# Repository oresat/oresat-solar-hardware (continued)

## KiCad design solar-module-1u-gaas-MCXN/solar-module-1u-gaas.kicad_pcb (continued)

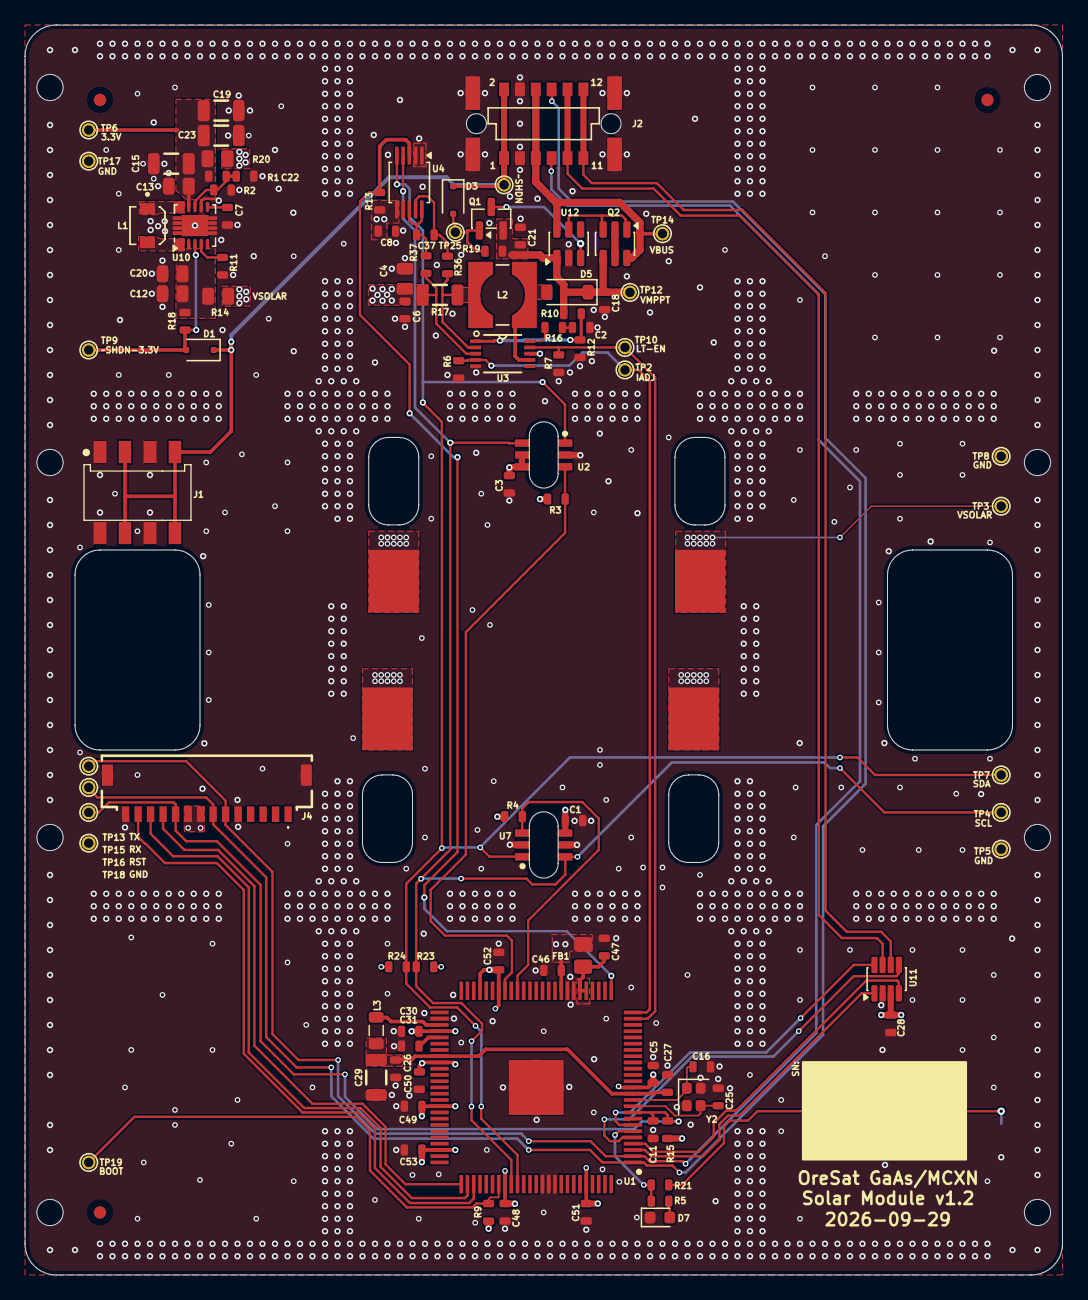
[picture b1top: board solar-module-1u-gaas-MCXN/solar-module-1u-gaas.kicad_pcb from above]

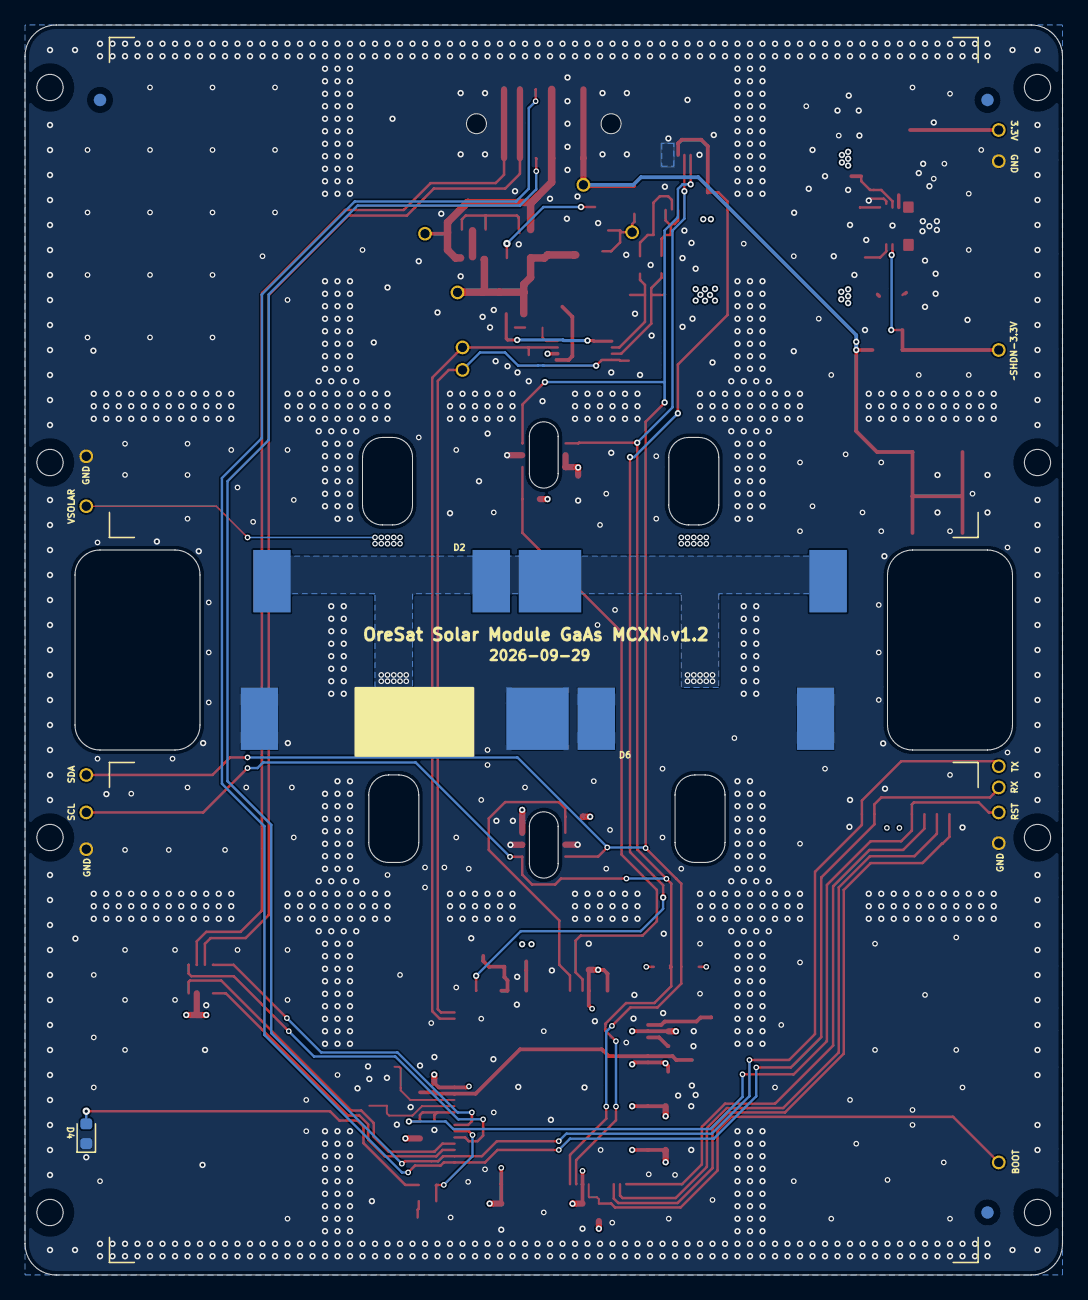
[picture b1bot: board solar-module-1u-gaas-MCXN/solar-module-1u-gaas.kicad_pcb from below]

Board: 4 copper layers, 83.0 x 100.0 mm, 110 parts (6 on the bottom side), 55 nets.

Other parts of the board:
PCB1: ORESAT-SOLAR-BOARD-V1.0-SILICON-CELLS; ORESAT-SOLAR-BOARD-V4

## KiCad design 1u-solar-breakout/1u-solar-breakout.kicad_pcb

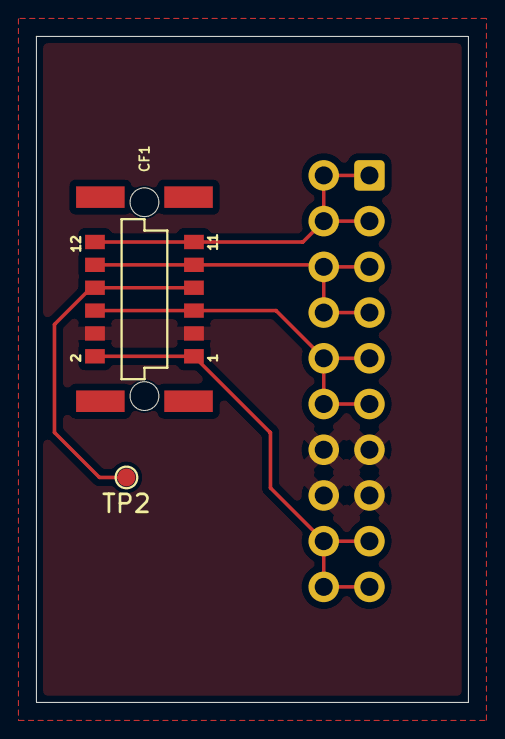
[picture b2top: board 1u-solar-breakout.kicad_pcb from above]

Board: 2 copper layers, 24.0 x 37.0 mm, 3 parts (1 on the bottom side), 6 nets.

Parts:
CF1: J-Harwin-M55-60X1242R
J3: 302-S201; IDC-Header_2x10_P2.54mm_Vertical
TP2: TEST-POINT-LARGE-SQUARE; TestPoint_Pad_D1.0mm

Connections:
GND: CF1.3 (GND), CF1.4 (GND), J3.13, J3.14, J3.15, J3.16
unnamed: CF1.7 (AUX), CF1.8 (AUX), TP2.1 (1_1)
unnamed: CF1.11 (CANL), CF1.12 (CANL), J3.1, J3.2, J3.3, J3.4
unnamed: CF1.9 (CANH), CF1.10 (CANH), J3.5, J3.6, J3.7, J3.8
unnamed: CF1.5 (VBUS), CF1.6 (VBUS), J3.9, J3.10, J3.11, J3.12
unnamed: CF1.1 (~SD), CF1.2 (~SD), J3.17, J3.18, J3.19, J3.20

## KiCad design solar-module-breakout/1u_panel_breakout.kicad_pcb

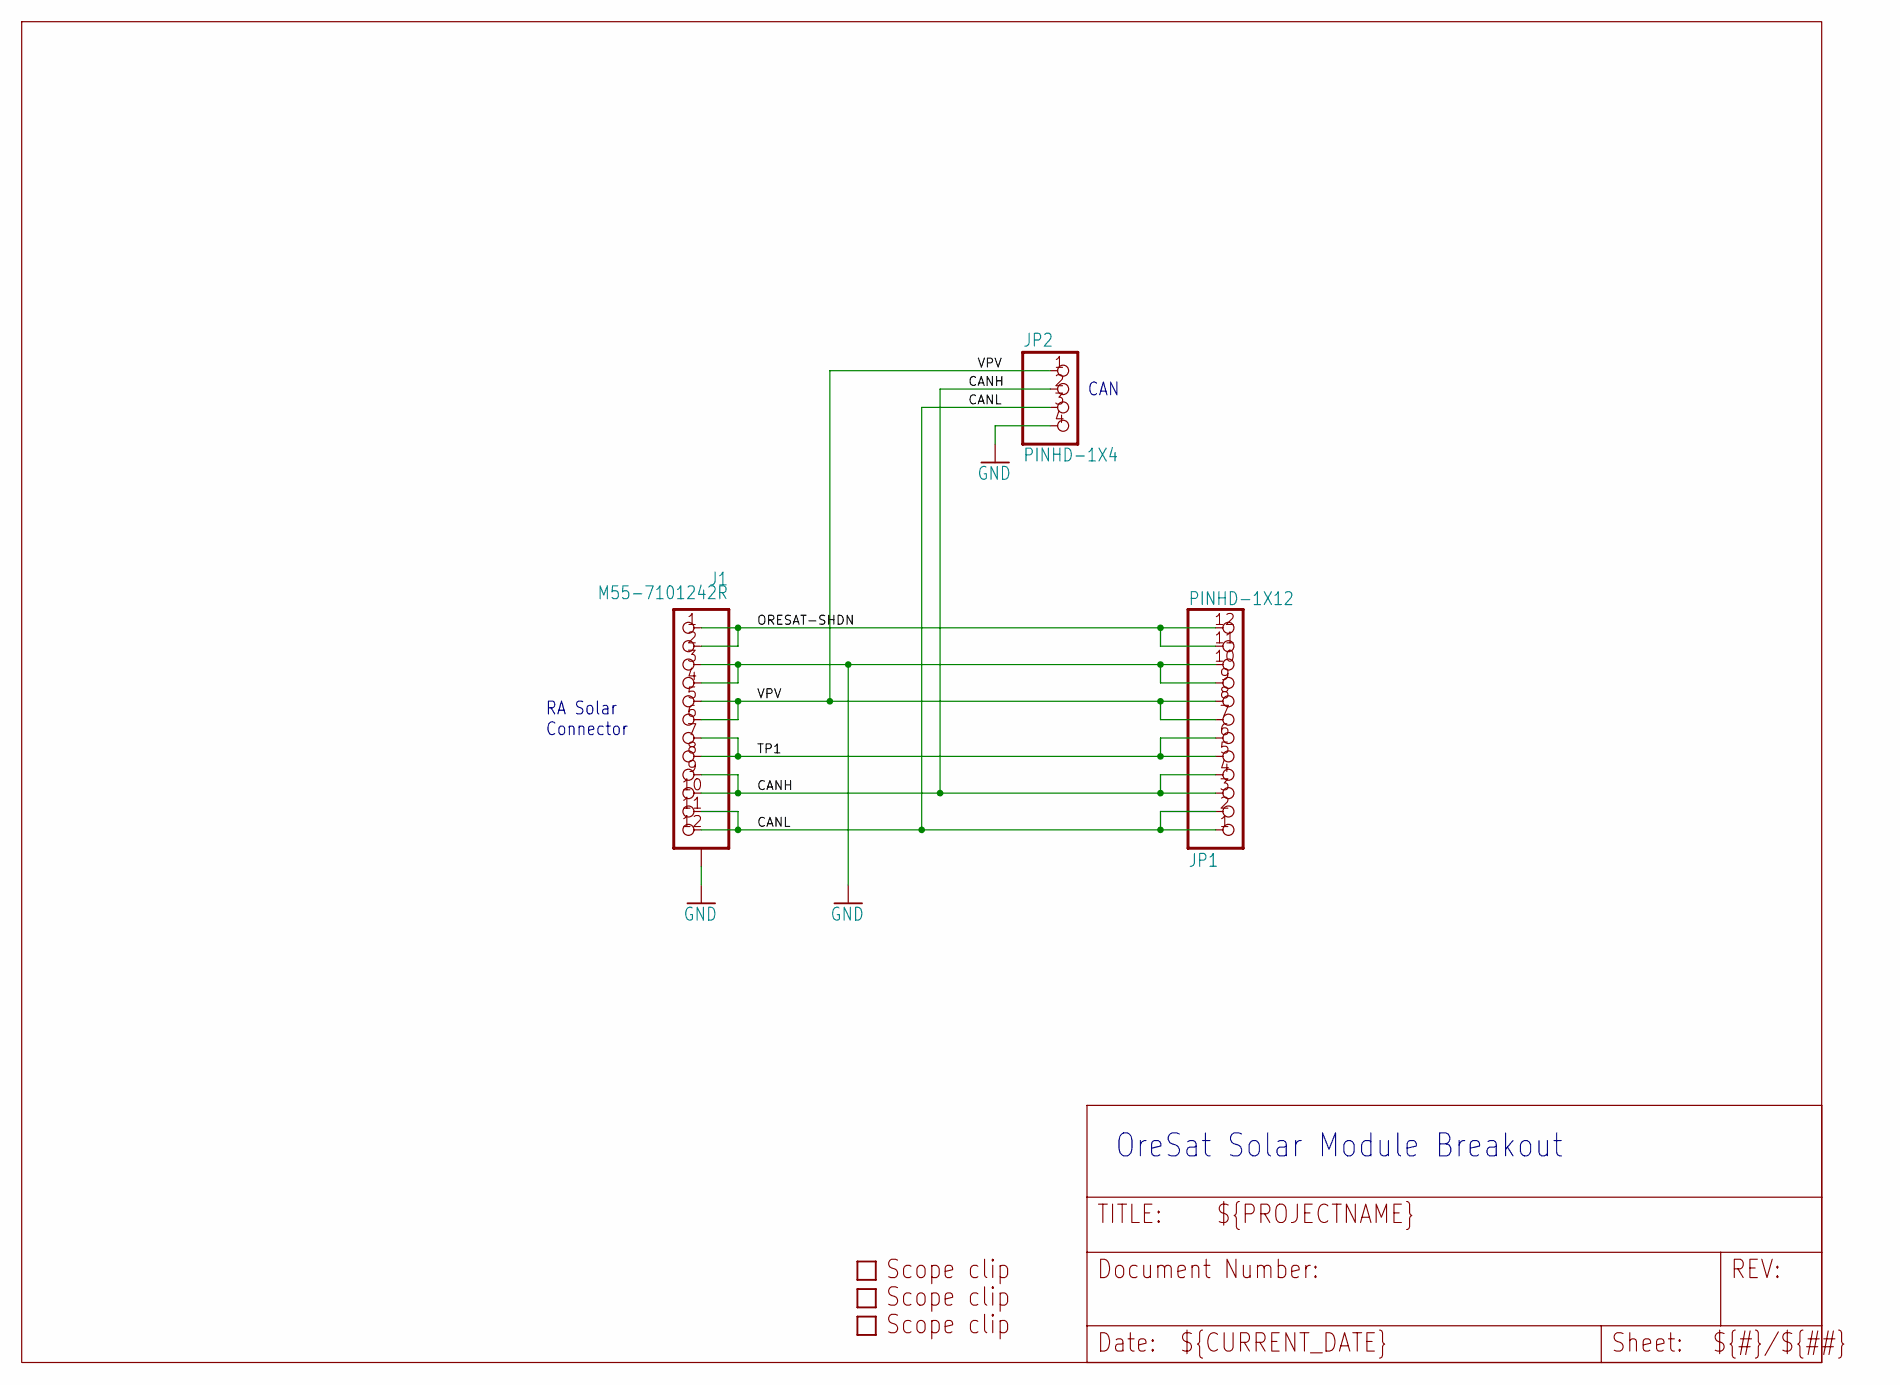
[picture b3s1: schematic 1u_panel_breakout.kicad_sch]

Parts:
J1: M55-7101242R
JP1: PINHD-1X12; 1X12
JP2: PINHD-1X4; 1X04
U$1, U$2, U$3: SCOPE_CLIP

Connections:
CANH: J1.9, J1.10, JP1.3, JP1.4, JP2.2
CANL: J1.11, J1.12, JP1.1, JP1.2, JP2.3
GND: J1.3, J1.4, J1.P$1 (SHIELD), J1.P$2 (SHIELD), J1.P$3 (SHIELD), J1.P$4 (SHIELD), JP1.9, JP1.10, JP2.4
ORESAT-SHDN: J1.1, J1.2, JP1.11, JP1.12
TP1: J1.7, J1.8, JP1.5, JP1.6
VPV: J1.5, J1.6, JP1.7, JP1.8, JP2.1

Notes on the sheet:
CAN
OreSat Solar Module Breakout
RA Solar Connector

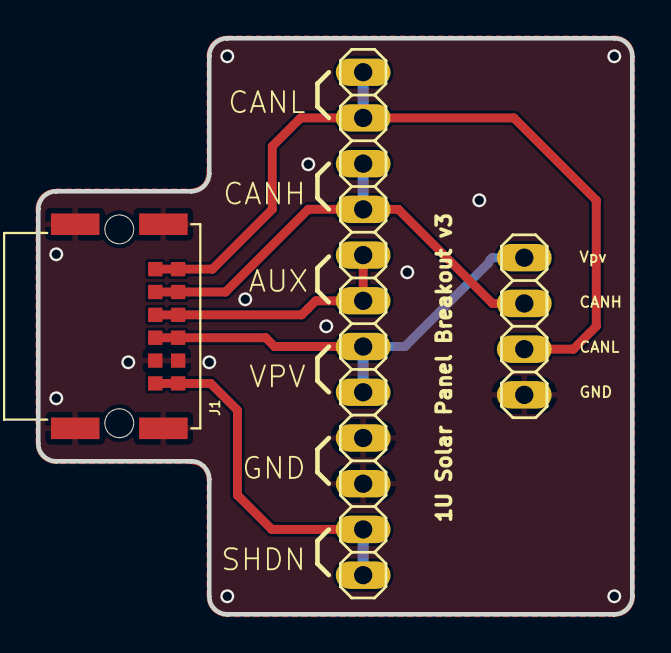
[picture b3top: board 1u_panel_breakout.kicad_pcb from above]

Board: 2 copper layers, 33.0 x 32.0 mm, 6 parts (0 on the bottom side), 6 nets.

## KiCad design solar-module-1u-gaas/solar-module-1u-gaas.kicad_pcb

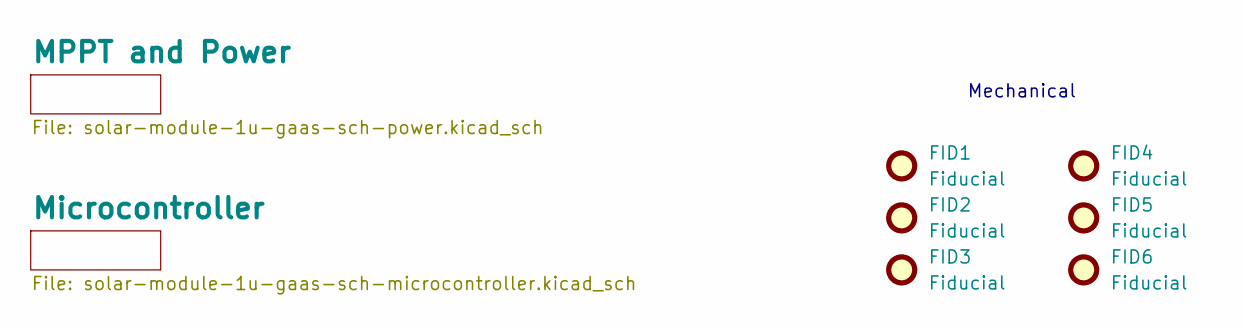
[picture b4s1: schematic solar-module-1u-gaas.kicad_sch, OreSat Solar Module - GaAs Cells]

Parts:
FID1, FID2, FID3, FID4, FID5, FID6: Fiducial; Fiducial_1mm_Mask2mm

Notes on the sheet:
Mechanical

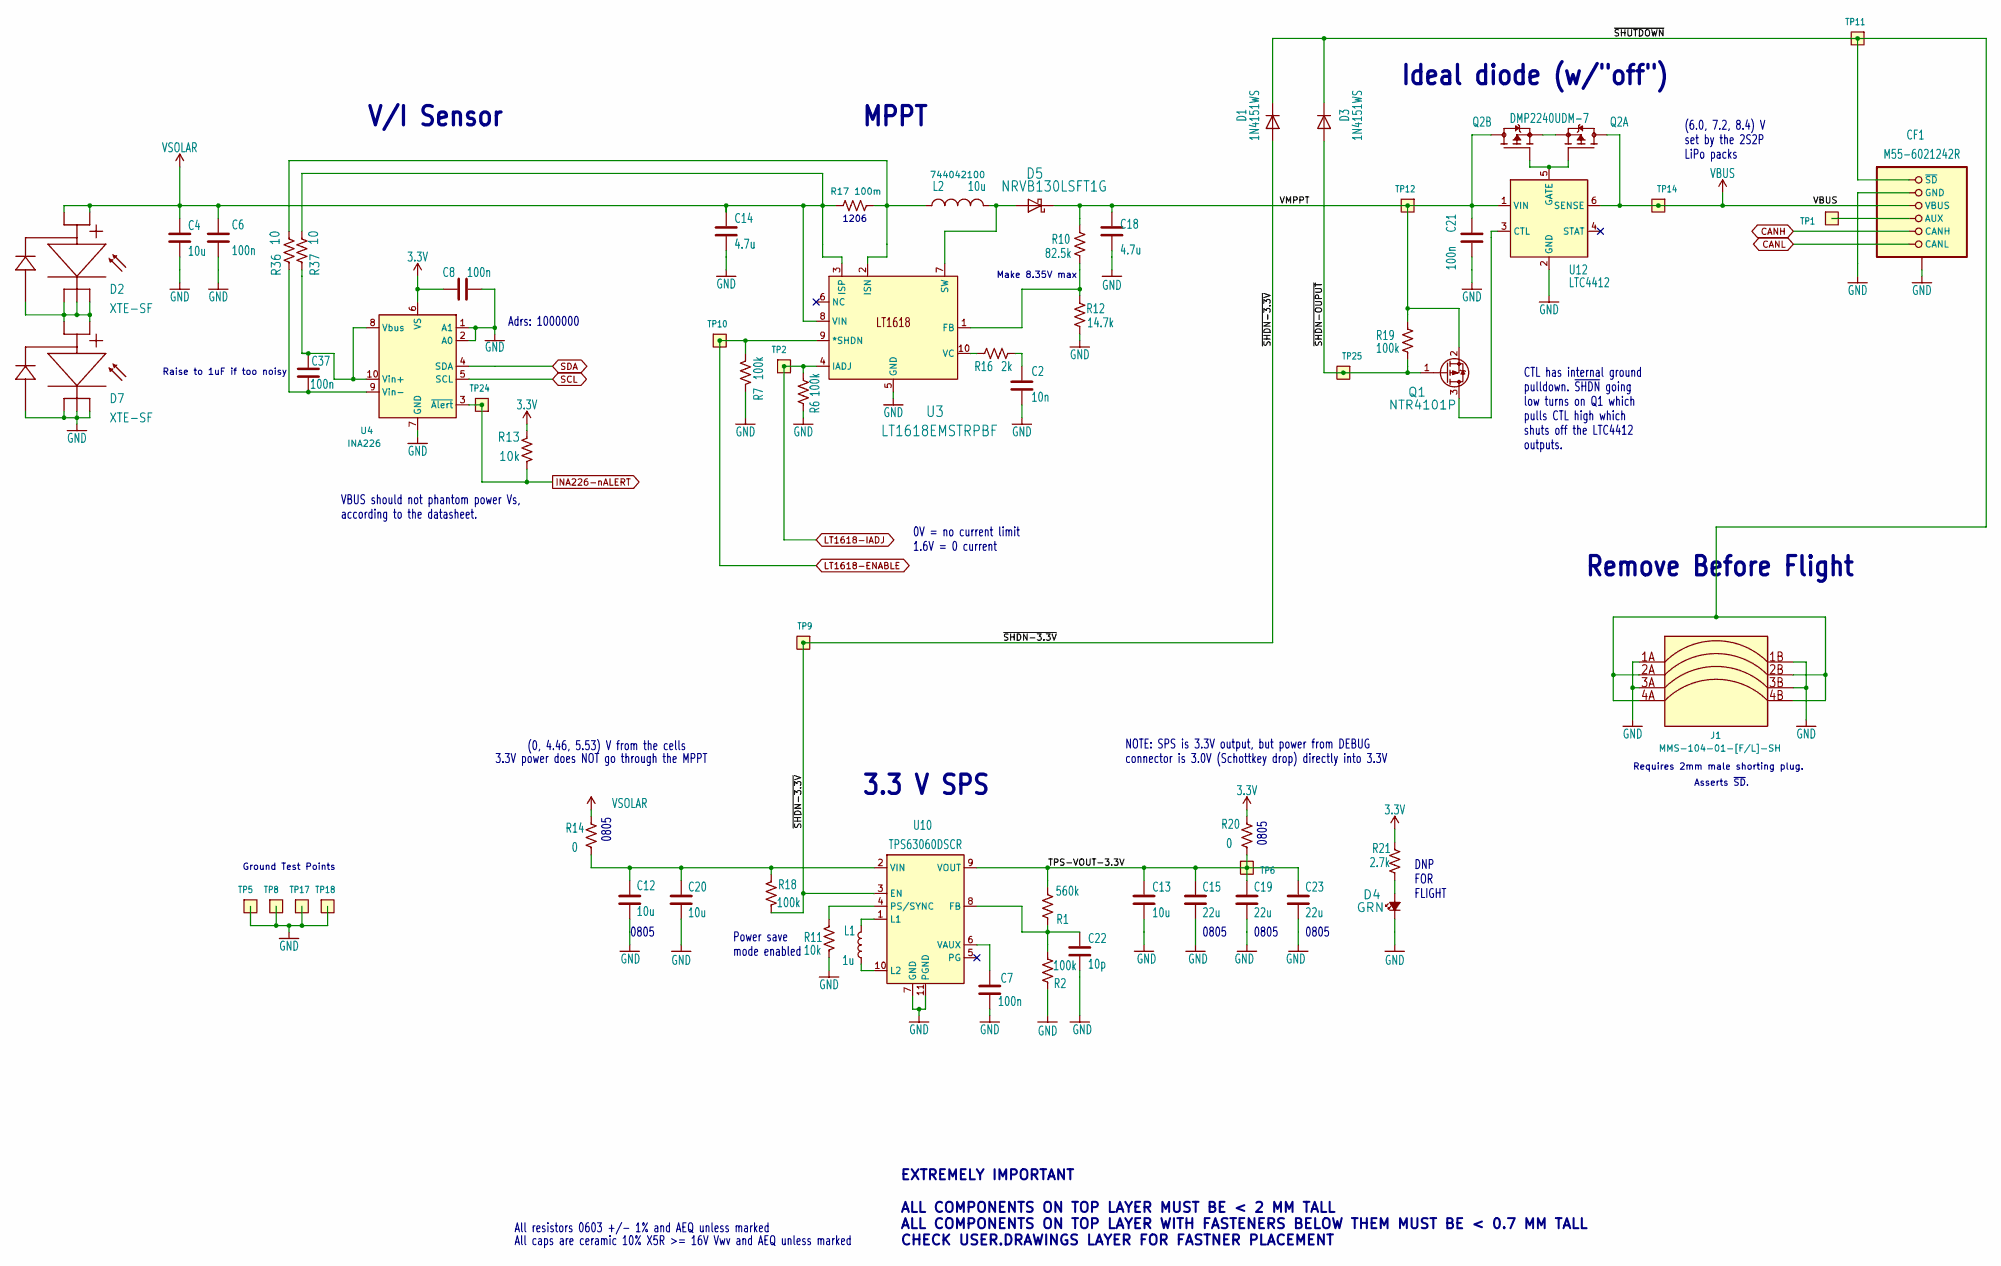
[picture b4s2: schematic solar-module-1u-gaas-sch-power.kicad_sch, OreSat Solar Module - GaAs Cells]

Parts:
C2: 10n; 0603-C-NOSILK; MPN C0603C103J3GECAUTO
C4, C13, C20: 10u; 0603-C-NOSILK; MPN GRT188R61C106KE13D
C6, C7, C8, C21, C37: 100n; 0603-C-NOSILK; MPN TMK107BJ104KAHT
C12: 10u; 0805-C-NOSILK; MPN GRT21BC71E106KE13L
C14, C18: 4.7u; 0603-C-NOSILK; MPN CL10A475KO8NNNC
C15, C19, C23: 22u; 0805-C-NOSILK; MPN 490-12389-2-ND
C22: 10p; 0603-C-NOSILK; MPN C0603C100J5GACAUTO
CF1: M55-6021242R; J-Harwin-M55-60X1242R; MPN M55-6021242R
D1, D3: 1N4151WS; D-SOD323-R; MPN 1N4151WS-E3-08
D2, D7: XTE-SF; SPECTROLAB-XTE-SF
D4: GRN; LED_0603_1608Metric; MPN 150060GS75000
D5: NRVB130LSFT1G; D_SOD-123; MPN NRVB130LSFT1G
J1: MMS-104-01-[F/L]-SH; SAMTEC-MMS-104-02-X-SH; MPN MMS-104-02-L-SH
L1: 1u; IND_1226AS-H-1R0N=P2; MPN 1227AS-H-1R0N=P2
L2: 10u; 744042100; MPN 744042100
Q1: NTR4101P; SOT-23; MPN NTR4101PT1G
Q2: DMP2240UDM-7; SOT-23-6; MPN DMP2240UDM-7
R1: 560k; 0603-C-NOSILK; MPN RMCF0603FT560K
R2, R6, R7, R18, R19: 100k; 0603-C-NOSILK; MPN RMCF0603FT100K
R10: 82.5k; 0603-C-NOSILK; MPN RMCF0603FT82K5
R11, R13: 10k; 0603-C-NOSILK; MPN RMCF0603FT10K0
R12: 14.7k; 0603-C-NOSILK; MPN RMCF0603FT14K7
R14, R20: 0; 0805-C-NOSILK; MPN ERJ-6GEY0R00V
R16: 2k; 0603-C-NOSILK; MPN RMCF0603FT2K00
R17: 100m; 1206-C; MPN CSR1206FTR100
R21: 2.7k; 0603-C-NOSILK; MPN RMCF0603FT2K70
R36, R37: 10; 0603-C-NOSILK; MPN RMCF0603FT10R0
TP1, TP2, TP5, TP6, TP8, TP9, TP10, TP11, TP12, TP14, TP17, TP18, TP24, TP25: TEST-POINT-LARGE-SQUARE; TestPoint-0.75mm-th
U3: LT1618EMSTRPBF; MSOP-10_MS; MPN IC REG BOOST ADJ 1.5A 10MSOP
U4: INA226; VSSOP-10_3x3mm_P0.5mm; MPN INA226AIDGST
U10: TPS63060DSCR; Texas_S-PWSON-N10; MPN IC REG BUCK BOOST ADJ 2A 10WSON
U12: LTC4412; TSOT-23-6; MPN LTC4412ES6#TRPBF

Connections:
3.3V: C8.1, R13.2, R20.1, R21.1, U4.6 (VS); also elsewhere on the board
/MPPT and Power/TPS-VOUT-3.3V: C13.1, C15.1, C19.1, C23.1, R1.2, R20.2, TP6.1, U10.9 (VOUT)
/MPPT and Power/VMPPT: C18.1, C21.1, D5.1 (K), Q1.2 (S), Q2.4 (D), R10.2, R19.2, TP12.1, U12.1 (VIN)
/MPPT and Power/~SHDN-3.3V: D1.2 (A), R18.1, TP9.1, U10.3 (EN)
/MPPT and Power/~SHDN-OUPUT: D3.2 (A), Q1.1 (G), R19.1, TP25.1
/MPPT and Power/~SHUTDOWN: CF1.1 (~SD), CF1.2 (~SD), D1.1 (K), D3.1 (K), J1.2A, J1.2B, J1.4A, J1.4B, TP11.1
CANH: CF1.9 (CANH), CF1.10 (CANH); also elsewhere on the board
CANL: CF1.11 (CANL), CF1.12 (CANL); also elsewhere on the board
GND: C2.2, C4.2, C6.2, C7.2, C8.2, C12.2, C13.2, C14.2, C15.2, C18.2, C19.2, C20.2, C21.2, C22.2, C23.2, CF1.3 (GND), CF1.4 (GND), CF1.P$1 (SHIELD), CF1.P$2 (SHIELD), CF1.P$3 (SHIELD), CF1.P$4 (SHIELD), D4.1 (K), D7.NEG1 (C1), D7.NEG2 (C2), D7.NEG3 (C3), D7.NEG4 (C4), J1.1A, J1.1B, J1.3A, J1.3B, R2.1, R6.2, R7.2, R11.1, R12.1, TP5.1, TP8.1, TP17.1, TP18.1, U3.5 (GND), U4.1 (A1), U4.2 (A0), U4.7 (GND), U10.7 (GND), U10.11 (PGND), U12.2 (GND); also elsewhere on the board
INA226-nALERT: R13.1, TP24.1, U4.3 (~Alert); also elsewhere on the board
LT1618-ENABLE: R7.1, TP10.1, U3.9 (*SHDN); also elsewhere on the board
LT1618-IADJ: R6.1, TP2.1, U3.4 (IADJ); also elsewhere on the board
unnamed: C2.1, R16.1
unnamed: CF1.7 (AUX), CF1.8 (AUX), TP1.1
unnamed: D2.NEG1 (C1), D2.NEG2 (C2), D2.NEG3 (C3), D2.NEG4 (C4), D7.POS1 (A1), D7.POS2 (A2)
unnamed: D4.2 (A), R21.2
unnamed: D5.2 (A), L2.2, U3.7 (SW)
unnamed: Q1.3 (D), U12.3 (CTL)
unnamed: Q2.1 (G), Q2.3 (G), U12.5 (GATE)
unnamed: Q2.2 (S), Q2.5 (S)
unnamed: R10.1, R12.2, U3.1 (FB)
unnamed: L2.1, R17.2, R36.1, U3.2 (ISN)
unnamed: R16.2, U3.10 (VC)
unnamed: C37.1, R37.1, U4.8 (Vbus), U4.10 (Vin+)
unnamed: C37.2, R36.2, U4.9 (Vin-)
unnamed: C22.1, R1.1, R2.2, U10.8 (FB)
unnamed: L1.2, U10.1 (L1)
unnamed: L1.1, U10.10 (L2)
unnamed: R11.2, U10.4 (PS/SYNC)
unnamed: C7.1, U10.6 (VAUX)
unnamed: C12.1, C20.1, R14.1, R18.2, U10.2 (VIN)
SCL: U4.5 (SCL); also elsewhere on the board
SDA: U4.4 (SDA); also elsewhere on the board
VBUS: CF1.5 (VBUS), CF1.6 (VBUS), Q2.6 (D), TP14.1, U12.6 (SENSE)
VSOLAR: C4.1, C6.1, C14.1, D2.POS1 (A1), D2.POS2 (A2), R14.2, R17.1, R37.2, U3.3 (ISP), U3.8 (VIN)

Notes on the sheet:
DNP FOR FLIGHT
0805
CTL has internal ground pulldown. ~{SHDN} going low turns on Q1 which pulls CTL high which shuts off the LTC4412 outputs.
(0, 4.46, 5.53) V from the cells
Ground Test Points
Make 8.35V max
Asserts ~{SD}.
Raise to 1uF if too noisy
All resistors 0603 +/- 1% and AEQ unless marked
NOTE: SPS is 3.3V output, but power from DEBUG connector is 3.0V (Schottkey drop) directly into 3.3V
Power save mode enabled
3.3 V SPS
EXTREMELY IMPORTANT ALL COMPONENTS ON TOP LAYER MUST BE < 2 MM TALL ALL COMPONENTS ON TOP LAYER WITH FASTENERS BELOW THEM MUST BE < 0.7 MM TALL CHECK USER.DRAWINGS LAYER FOR FASTNER PLACEMENT
MPPT
All caps are ceramic 10% X5R >= 16V Vwv and AEQ unless marked
Ideal diode (w/"off")
VBUS should not phantom power Vs, according to the datasheet.
3.3V power does NOT go through the MPPT
Remove Before Flight
V/I Sensor
0V = no current limit 1.6V = 0 current
1206
Adrs: 1000000
(6.0, 7.2, 8.4) V set by the 2S2P LiPo packs
Requires 2mm male shorting plug.

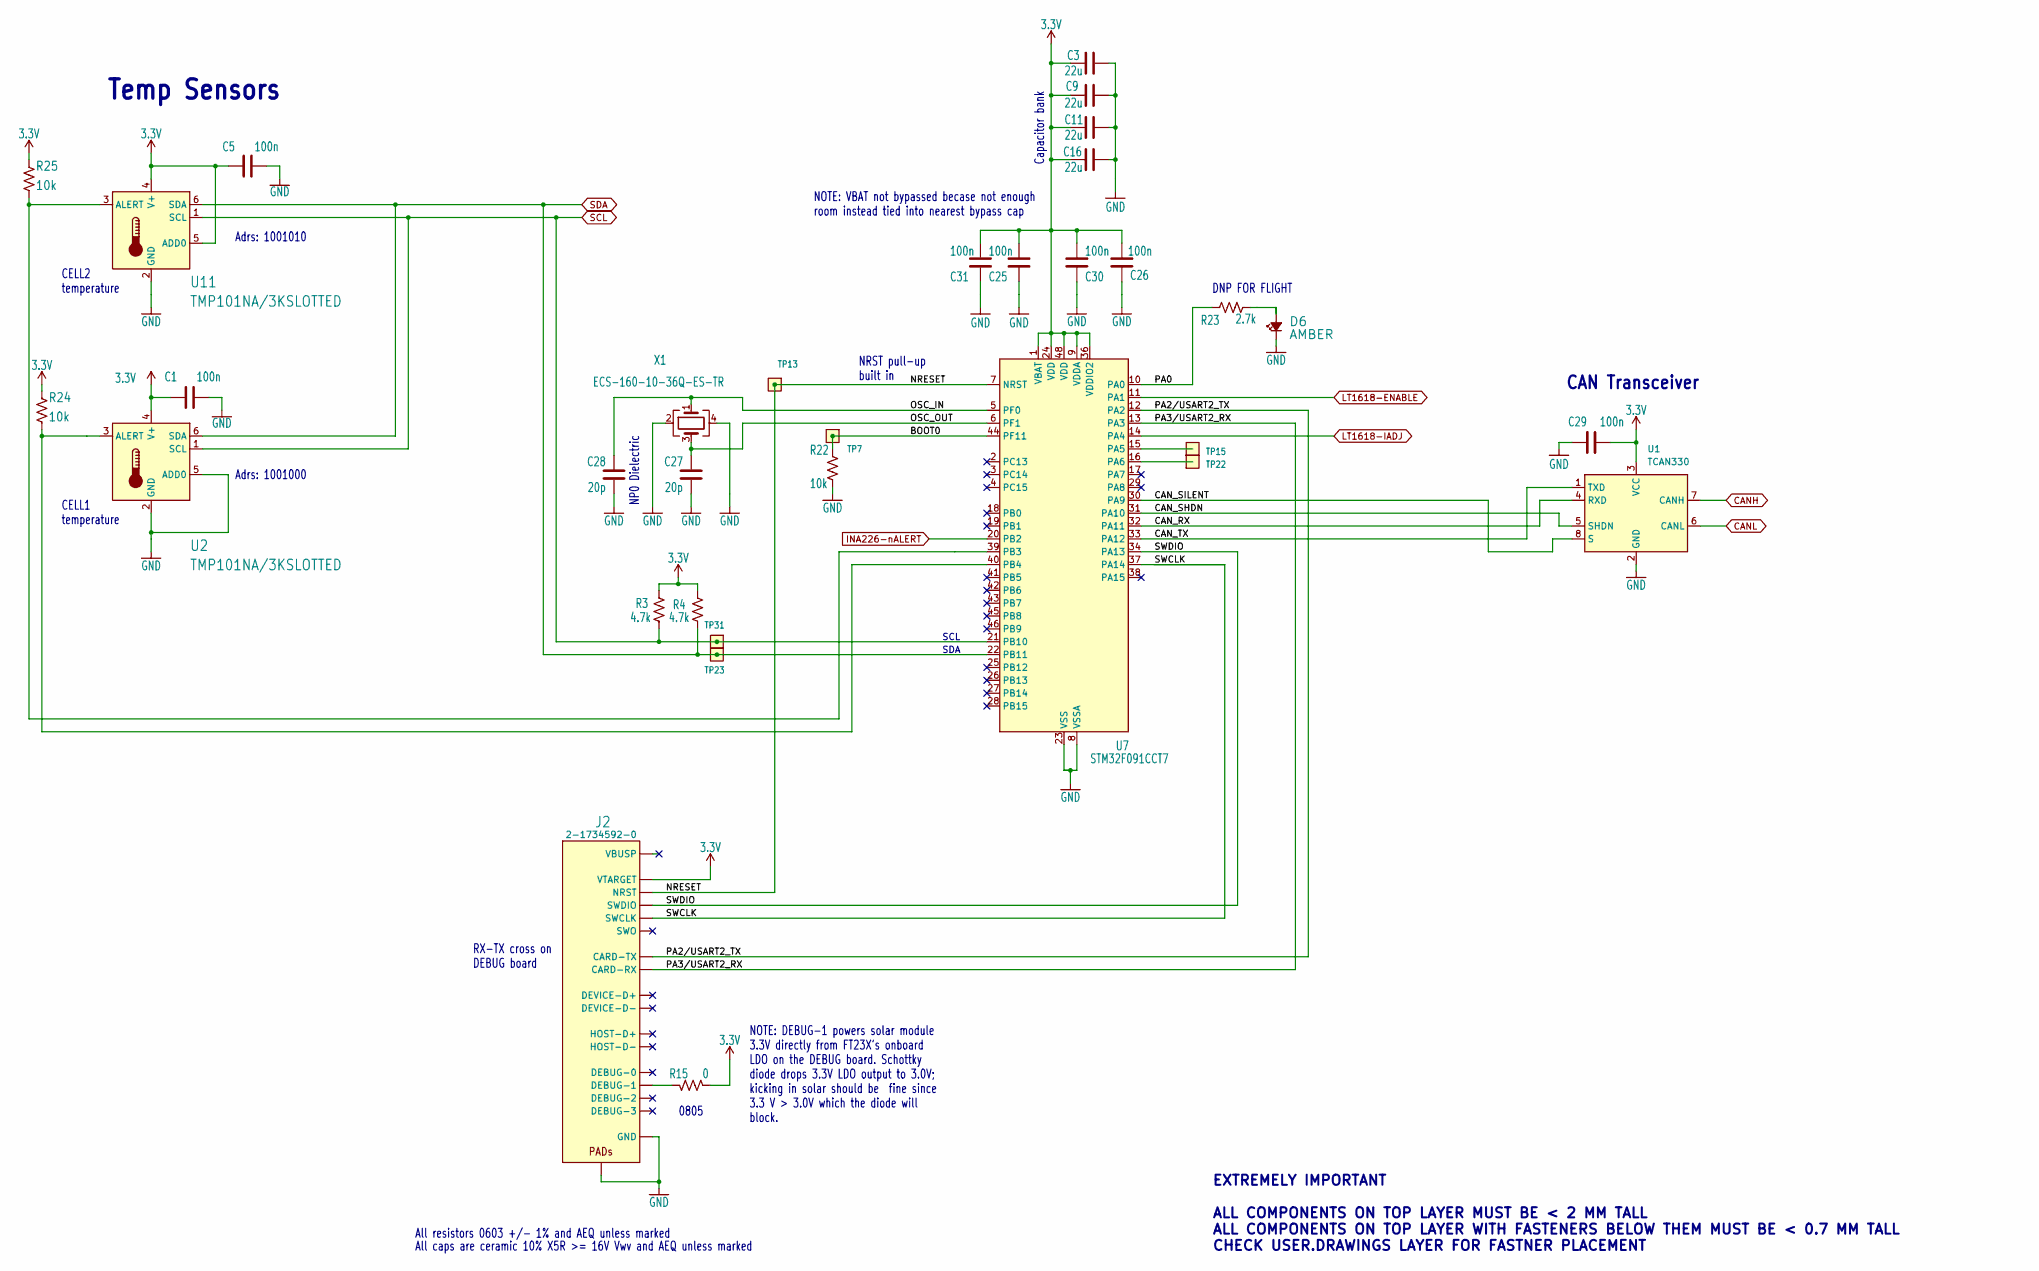
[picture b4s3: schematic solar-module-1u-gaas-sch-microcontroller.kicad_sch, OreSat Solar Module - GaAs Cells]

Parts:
C1, C5, C25, C26, C29, C30, C31: 100n; 0603-C-NOSILK; MPN TMK107BJ104KAHT
C3, C9, C11, C16: 22u; 0805-C-NOSILK; MPN 490-12389-2-ND
C27, C28: 20p; 0603-C-NOSILK; MPN C0603C200J5GACAUTO
D6: AMBER; LED_0603_1608Metric; MPN 150060AS75000
J2: 2-1734592-0; J-TE-2-1734592-0; MPN 2-1734592-0
R3, R4: 4.7k; 0603-C-NOSILK; MPN RMCF0603FT4K70
R15: 0; 0805-C-NOSILK; MPN ERJ-6GEY0R00V
R22, R24, R25: 10k; 0603-C-NOSILK; MPN RMCF0603FT10K0
R23: 2.7k; 0603-C-NOSILK; MPN RMCF0603FT2K70
TP7, TP13, TP15, TP22, TP23, TP31: TEST-POINT-LARGE-SQUARE; TestPoint-0.75mm-th
U1: TCAN330; SOT-23-8; MPN TCAN330GDCNT
U2, U11: TMP101NA/3KSLOTTED; DBV6-SLOT; MPN TMP101NA/3K
U7: STM32F091CCT7; LQFP-48_7x7mm_P0.5mm; MPN STM32F091CCT7TR
X1: ECS-160-10-36Q-ES-TR; MPN ECS-160-10-36Q-ES-TR

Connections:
3.3V: C1.1, C3.1, C5.1, C9.1, C11.1, C16.1, C25.2, C26.2, C29.2, C30.2, C31.2, J2.11 (VTARGET), R3.2, R4.2, R15.2, R24.2, R25.2, U1.3 (VCC), U2.4 (V+), U7.1 (VBAT), U7.9 (VDDA), U7.24 (VDD), U7.36 (VDDIO2), U7.48 (VDD), U11.4 (V+), U11.5 (ADD0); also elsewhere on the board
/Microcontroller/BOOT0: R22.1, TP7.1, U7.44 (PF11)
/Microcontroller/CAN_RX: U1.4 (RXD), U7.32 (PA11)
/Microcontroller/CAN_SHDN: U1.5 (SHDN), U7.31 (PA10)
/Microcontroller/CAN_SILENT: U1.8 (S), U7.30 (PA9)
/Microcontroller/CAN_TX: U1.1 (TXD), U7.33 (PA12)
/Microcontroller/NRESET: J2.10 (NRST), TP13.1, U7.7 (NRST)
/Microcontroller/OSC_IN: C28.1, U7.5 (PF0), X1.1
/Microcontroller/OSC_OUT: C27.1, U7.6 (PF1), X1.3
/Microcontroller/PA0: R23.2, U7.10 (PA0)
/Microcontroller/PA2/USART2_TX: J2.13 (CARD-TX), U7.12 (PA2)
/Microcontroller/PA3/USART2_RX: J2.12 (CARD-RX), U7.13 (PA3)
/Microcontroller/SWCLK: J2.15 (SWCLK), U7.37 (PA14)
/Microcontroller/SWDIO: J2.14 (SWDIO), U7.34 (PA13)
CANH: U1.7 (CANH); also elsewhere on the board
CANL: U1.6 (CANL); also elsewhere on the board
GND: C1.2, C3.2, C5.2, C9.2, C11.2, C16.2, C25.1, C26.1, C27.2, C28.2, C29.1, C30.1, C31.1, D6.1 (K), J2.3 (GND), J2.6 (GND), J2.9 (GND), J2.PAD1 (PAD), J2.PAD2 (PAD), R22.2, U1.2 (GND), U2.2 (GND), U2.5 (ADD0), U7.8 (VSSA), U7.23 (VSS), U7.35 (VSS), U7.47 (VSS), U11.2 (GND), X1.2, X1.4; also elsewhere on the board
INA226-nALERT: U7.20 (PB2); also elsewhere on the board
LT1618-ENABLE: U7.11 (PA1); also elsewhere on the board
LT1618-IADJ: U7.14 (PA4); also elsewhere on the board
unnamed: D6.2 (A), R23.1
unnamed: J2.18 (DEBUG-1), R15.1
unnamed: R24.1, U2.3 (ALERT), U7.40 (PB4)
unnamed: TP15.1, U7.15 (PA5)
unnamed: TP22.1, U7.16 (PA6)
unnamed: R25.1, U7.39 (PB3), U11.3 (ALERT)
SCL: R3.1, TP31.1, U2.1 (SCL), U7.21 (PB10), U11.1 (SCL); also elsewhere on the board
SDA: R4.1, TP23.1, U2.6 (SDA), U7.22 (PB11), U11.6 (SDA); also elsewhere on the board

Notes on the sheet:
Capacitor bank
SDA
Temp Sensors
NOTE: VBAT not bypassed becase not enough room instead tied into nearest bypass cap
DNP FOR FLIGHT
NRST pull-up built in
CAN Transceiver
NP0 Dielectric
NOTE: DEBUG-1 powers solar module 3.3V directly from FT23X's onboard LDO on the DEBUG board. Schottky diode drops 3.3V LDO output to 3.0V; kicking in solar should be fine since 3.3 V > 3.0V which the diode will block.
Adrs: 1001010
Adrs: 1001000
CELL2 temperature
RX-TX cross on DEBUG board
EXTREMELY IMPORTANT ALL COMPONENTS ON TOP LAYER MUST BE < 2 MM TALL ALL COMPONENTS ON TOP LAYER WITH FASTENERS BELOW THEM MUST BE < 0.7 MM TALL CHECK USER.DRAWINGS LAYER FOR FASTNER PLACEMENT
SCL
All resistors 0603 +/- 1% and AEQ unless marked
CELL1 temperature
0805
All caps are ceramic 10% X5R >= 16V Vwv and AEQ unless marked

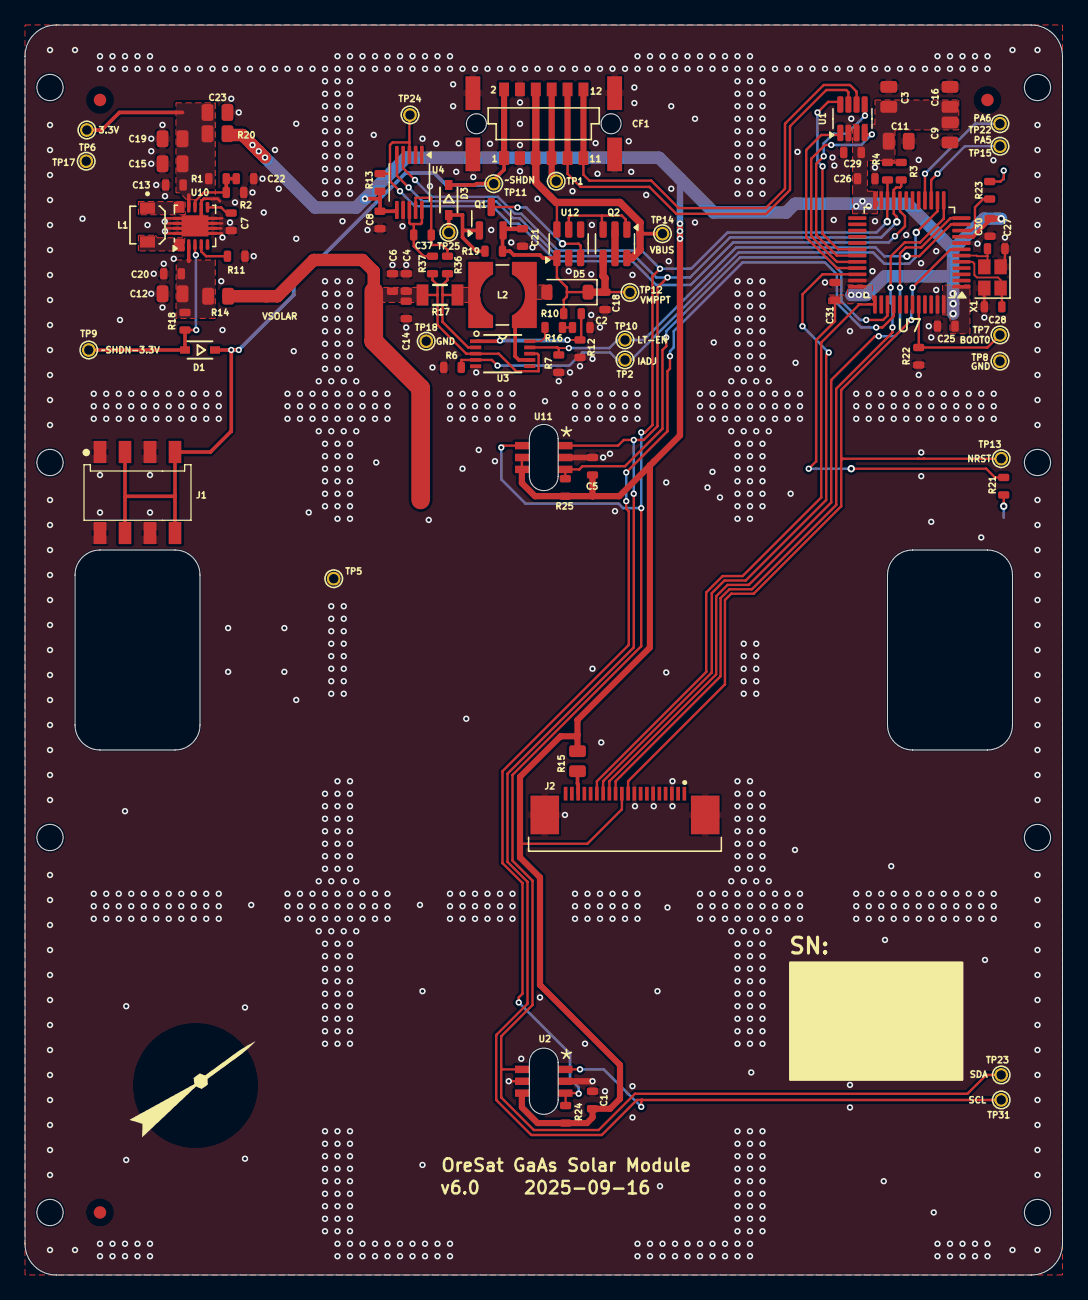
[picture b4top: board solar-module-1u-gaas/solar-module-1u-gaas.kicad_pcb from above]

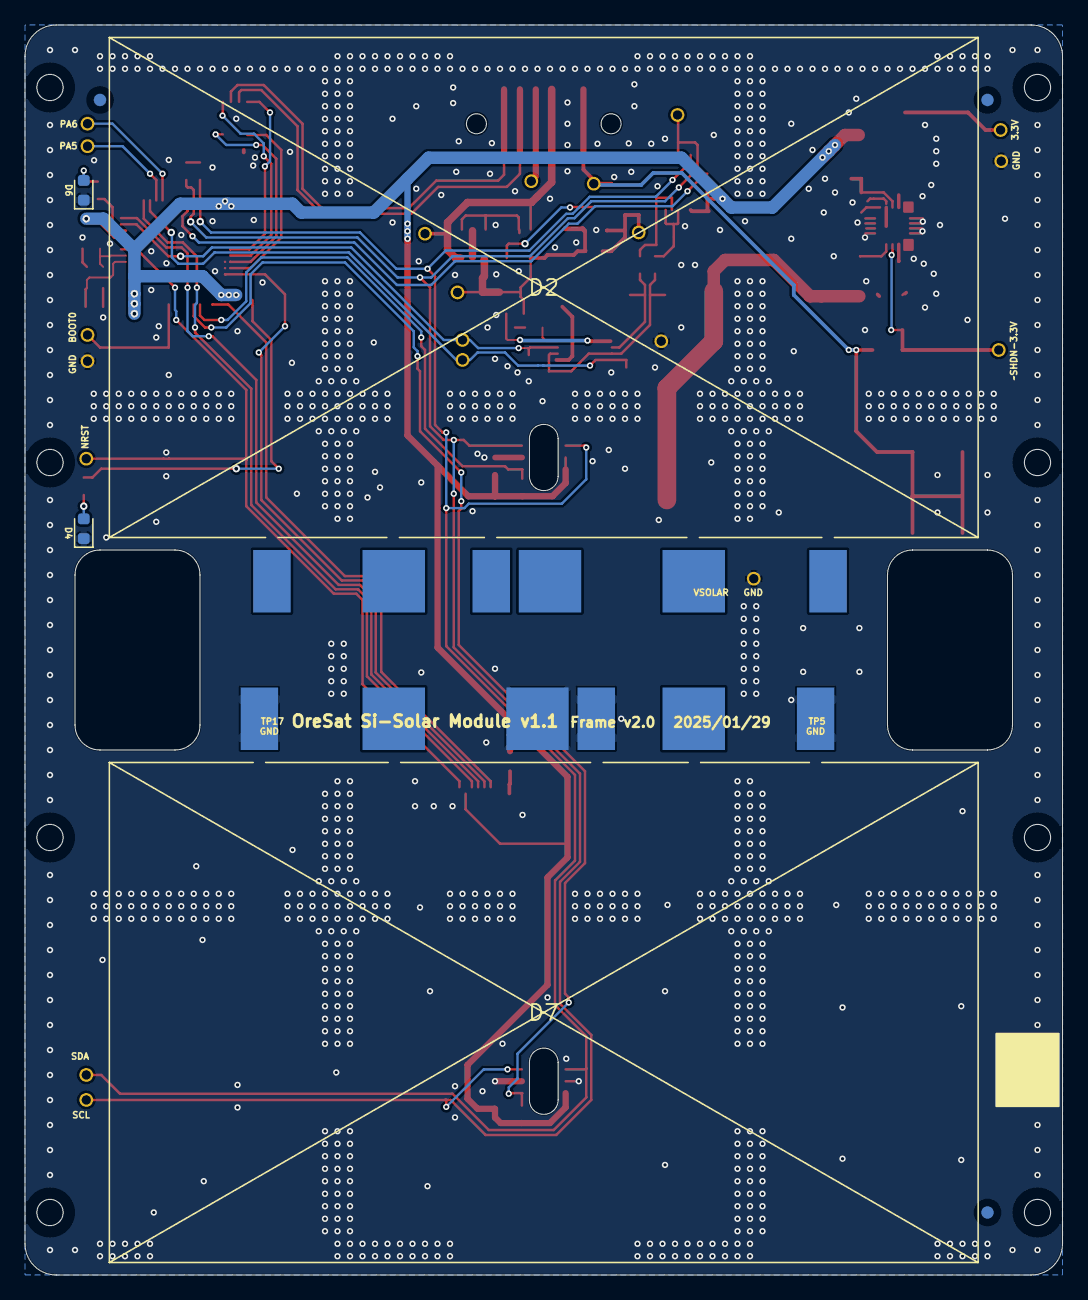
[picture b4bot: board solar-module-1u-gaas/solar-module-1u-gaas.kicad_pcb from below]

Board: 2 copper layers, 83.0 x 100.0 mm, 104 parts (7 on the bottom side), 54 nets.

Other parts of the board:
LOGO1: PSAS_LOGO_10X10
PCB1: ORESAT-SOLAR-BOARD-V1.0-SILICON-CELLS; ORESAT-SOLAR-BOARD-V4
